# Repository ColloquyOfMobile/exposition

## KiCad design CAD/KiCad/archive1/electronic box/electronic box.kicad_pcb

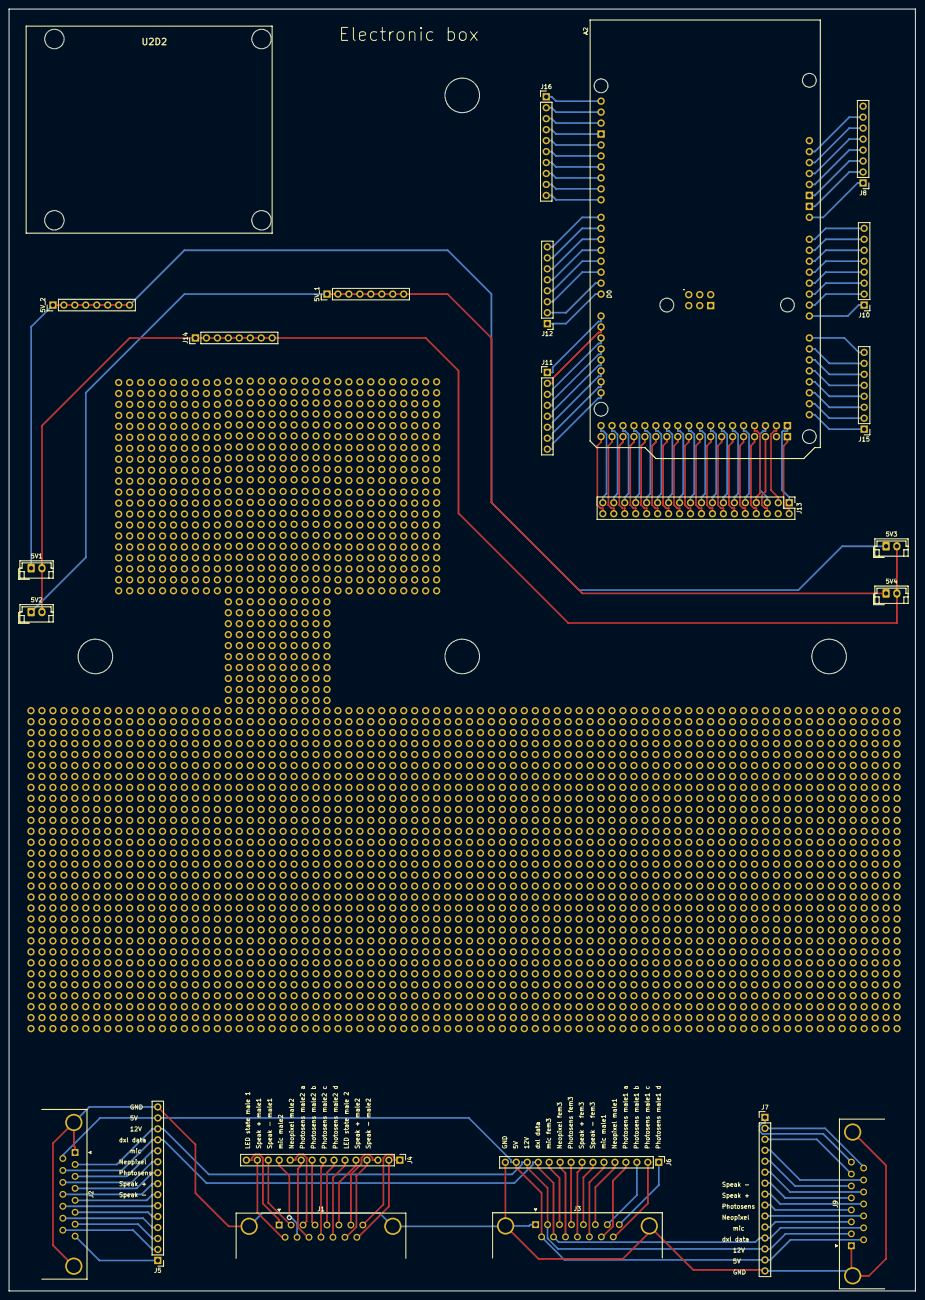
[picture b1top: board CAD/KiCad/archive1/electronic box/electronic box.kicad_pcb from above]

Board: 2 copper layers, 210.0 x 297.0 mm, 54 parts (1 on the bottom side), 139 nets.

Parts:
5V1, 5V3: 5V1; JST_EH_B2B-EH-A_1x02_P2.50mm_Vertical
5V2, 5V4: 5V2; JST_EH_B2B-EH-A_1x02_P2.50mm_Vertical
5V_1, 5V_2: Conn_01x08; PinHeader_1x08_P2.54mm_Vertical
A2: Arduino_Mega2560_R3_Shield
J1: to center B; DSUB-15_Male_Horizontal_P2.77x2.84mm_EdgePinOffset4.94mm_Ho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
J2: to female static 1; DSUB-15_Male_Horizontal_P2.77x2.84mm_EdgePinOffset4.94mm_Ho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
J3: to center A; DSUB-15_Male_Horizontal_P2.77x2.84mm_EdgePinOffset4.94mm_Ho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
J4, J5, J6, J7: Conn_01x15; PinHeader_1x15_P2.54mm_Vertical
J8, J10, J11, J12, J14, J15: Conn_01x08; PinHeader_1x08_P2.54mm_Vertical
J9: to female static 2; DSUB-15_Male_Horizontal_P2.77x2.84mm_EdgePinOffset4.94mm_Ho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
J13: Conn_02x18_Odd_Even; PinHeader_2x18_P2.54mm_Vertical
J16: Conn_01x10; PinHeader_1x10_P2.54mm_Vertical
U1, U2, U3, U4, U5, U6, U7, U8, U9, U10, U11, U12, U13, U14, U15, U16, U17, U18, U19, U20, U21, U22, U23, U24, U25, U26, U27, U28, U29, U30, U31: test_pad_10x10

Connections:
/Arduino Mega/5V3: A2.5V3 (5V), J13.35
/Arduino Mega/5V4: A2.5V4 (5V), J13.36
/Arduino Mega/D0: A2.D0 (D0/RX0), J12.1
/Arduino Mega/D1: A2.D1 (D1/TX0), J12.2
/Arduino Mega/D08: A2.D8, J16.10
/Arduino Mega/D09: A2.D9, J16.9
/Arduino Mega/D10: A2.D10, J16.8
/Arduino Mega/D11: A2.D11, J16.7
/Arduino Mega/D12: A2.D12, J16.6
/Arduino Mega/D13: A2.D13, J16.5
/Arduino Mega/D20: A2.D20 (D20/SDA), J11.7
/Arduino Mega/D21: A2.D21 (D21/SCL), J11.8
/Arduino Mega/D22: A2.D22, J13.33
/Arduino Mega/D23: A2.D23, J13.34
/Arduino Mega/D24: A2.D24, J13.31
/Arduino Mega/D25: A2.D25, J13.32
/Arduino Mega/D26: A2.D26, J13.29
/Arduino Mega/D27: A2.D27, J13.30
/Arduino Mega/D28: A2.D28, J13.27
/Arduino Mega/D29: A2.D29, J13.28
/Arduino Mega/D30: A2.D30, J13.25
/Arduino Mega/D31: A2.D31, J13.26
/Arduino Mega/D32: A2.D32, J13.23
/Arduino Mega/D33: A2.D33, J13.24
/Arduino Mega/D34: A2.D34, J13.21
/Arduino Mega/D35: A2.D35, J13.22
/Arduino Mega/D36: A2.D36, J13.19
/Arduino Mega/D37: A2.D37, J13.20
/Arduino Mega/D38: A2.D38, J13.17
/Arduino Mega/D39: A2.D39, J13.18
/Arduino Mega/D40: A2.D40, J13.15
/Arduino Mega/D41: A2.D41, J13.16
/Arduino Mega/D42: A2.D42, J13.13
/Arduino Mega/D43: A2.D43, J13.14
/Arduino Mega/D44: A2.D44, J13.11
/Arduino Mega/D45: A2.D45, J13.12
/Arduino Mega/D46: A2.D46, J13.9
/Arduino Mega/D47: A2.D47, J13.10
/Arduino Mega/D48: A2.D48, J13.7
/Arduino Mega/D49: A2.D49, J13.8
/Arduino Mega/D50: A2.D50 (D50_MISO), J13.5
/Arduino Mega/D51: A2.D51 (D51_MOSI), J13.6
/Arduino Mega/D52: A2.D52 (D52_SCK), J13.3
/Arduino Mega/GND5: A2.GND5 (GND), J13.1
/Arduino Mega/GND6: A2.GND6 (GND), J13.2
/D-sub connectors/5V: J2.9, J3.9, J5.14, J6.14, J7.14, J9.9
/D-sub connectors/12V: J2.2, J3.2, J5.13, J6.13, J7.13, J9.2
/D-sub connectors/dynamixel data: J2.10, J3.10, J5.12, J6.12, J7.12, J9.10
/D-sub connectors/microphone female output: J3.3, J6.11
/D-sub connectors/microphone female output 1: J2.3, J5.11
/D-sub connectors/microphone female output 2: J7.11, J9.3
/D-sub connectors/microphone male output 1: J3.13, J6.6
/D-sub connectors/microphone male output 2: J1.10, J4.12
/D-sub connectors/neopixel female input: J3.11 (P111), J6.10
/D-sub connectors/neopixel female input 1: J2.11 (P111), J5.10
/D-sub connectors/neopixel female input 2: J7.10, J9.11 (P111)
/D-sub connectors/neopixel male input 1: J3.6, J6.5
/D-sub connectors/neopixel male input 2: J1.3, J4.11
/D-sub connectors/photo sensor female output: J3.4, J6.9
/D-sub connectors/photo sensor female output 1: J2.4, J5.9
/D-sub connectors/photo sensor female output 2: J7.9, J9.4
/D-sub connectors/photo sensor male output 1a: J3.14, J6.4
/D-sub connectors/photo sensor male output 1b: J3.7, J6.3
/D-sub connectors/photo sensor male output 1c: J3.15, J6.2
/D-sub connectors/photo sensor male output 1d: J3.8, J6.1
/D-sub connectors/photo sensor male output 2a: J1.11 (P111), J4.10
/D-sub connectors/photo sensor male output 2b: J1.4, J4.9
/D-sub connectors/photo sensor male output 2c: J1.12, J4.8
/D-sub connectors/photo sensor male output 2d: J1.5, J4.7
/D-sub connectors/speaker female 1 +: J2.12, J5.8
/D-sub connectors/speaker female 1 -: J2.5, J5.7
/D-sub connectors/speaker female 2 +: J7.8, J9.12
/D-sub connectors/speaker female 2 -: J7.7, J9.5
/D-sub connectors/speaker female +: J3.12, J6.8
/D-sub connectors/speaker female -: J3.5, J6.7
/D-sub connectors/speaker male 1 +: J1.9, J4.14
/D-sub connectors/speaker male 1 -: J1.2, J4.13
/D-sub connectors/speaker male 2 +: J1.6, J4.5
/D-sub connectors/speaker male 2 -: J1.14, J4.4
/D-sub connectors/state LED male output 1: J1.1, J4.15
/D-sub connectors/state LED male output 2: J1.13, J4.6
/Pad/5V1: 5V2.1, 5V4.1, 5V_1.1, 5V_1.2, 5V_1.3, 5V_1.4, 5V_1.5, 5V_1.6, 5V_1.7, 5V_1.8
/Pad/5V2: 5V1.1, 5V3.1, 5V_2.1, 5V_2.2, 5V_2.3, 5V_2.4, 5V_2.5, 5V_2.6, 5V_2.7, 5V_2.8
GND: J1.0 (PAD), J2.0 (PAD), J2.1, J3.0 (PAD), J3.1, J5.15, J6.15, J7.15, J9.0 (PAD), J9.1
GND1: 5V1.2, 5V2.2, 5V3.2, 5V4.2, J14.1, J14.2, J14.3, J14.4, J14.5, J14.6, J14.7, J14.8
unnamed: A2.3V3 (3.3V), J8.5
unnamed: A2.D2 (D2_INT0), J12.3
unnamed: A2.D3 (D3_INT1), J12.4
unnamed: A2.D14 (D14/TX3), J11.1
unnamed: A2.D15 (D15/RX3), J11.2
unnamed: A2.D16 (D16/TX2), J11.3
unnamed: A2.D17 (D17/RX2), J11.4
unnamed: A2.D18 (D18/TX1), J11.5
unnamed: A2.D19 (D19/RX1), J11.6
unnamed: A2.IORF (IOREF), J8.7
unnamed: A2.RST1 (RESET), J8.6
unnamed: J1.15, J4.2
unnamed: J2.13, J5.6
unnamed: J2.14, J5.4
unnamed: J2.15, J5.2
unnamed: J1.8, J4.1
unnamed: J1.7, J4.3
unnamed: J2.8, J5.1
unnamed: J2.7, J5.3
unnamed: J2.6, J5.5
unnamed: J7.1, J9.8
unnamed: J7.2, J9.15
unnamed: J7.3, J9.7
unnamed: J7.4, J9.14
unnamed: J7.5, J9.6
unnamed: J7.6, J9.13
unnamed: A2.VIN, J8.1
unnamed: A2.GND3 (GND), J8.2
unnamed: A2.GND2 (GND), J8.3
unnamed: A2.5V1 (5V), J8.4
unnamed: A2.A7, J10.1
unnamed: A2.A6, J10.2
unnamed: A2.A5, J10.3
unnamed: A2.A4, J10.4
unnamed: A2.A3, J10.5
unnamed: A2.A2, J10.6
unnamed: A2.A1, J10.7
unnamed: A2.A0, J10.8
unnamed: A2.D4, J12.5
unnamed: A2.D5, J12.6
unnamed: A2.D6, J12.7
unnamed: A2.D7, J12.8
unnamed: A2.A15, J15.1
unnamed: A2.A14, J15.2
unnamed: A2.A13, J15.3
unnamed: A2.A12, J15.4
unnamed: A2.A11, J15.5
unnamed: A2.A10, J15.6
unnamed: A2.A9, J15.7
unnamed: A2.A8, J15.8
unnamed: A2.SCL, J16.1
unnamed: A2.SDA, J16.2
unnamed: A2.AREF, J16.3
unnamed: A2.GND1 (GND), J16.4

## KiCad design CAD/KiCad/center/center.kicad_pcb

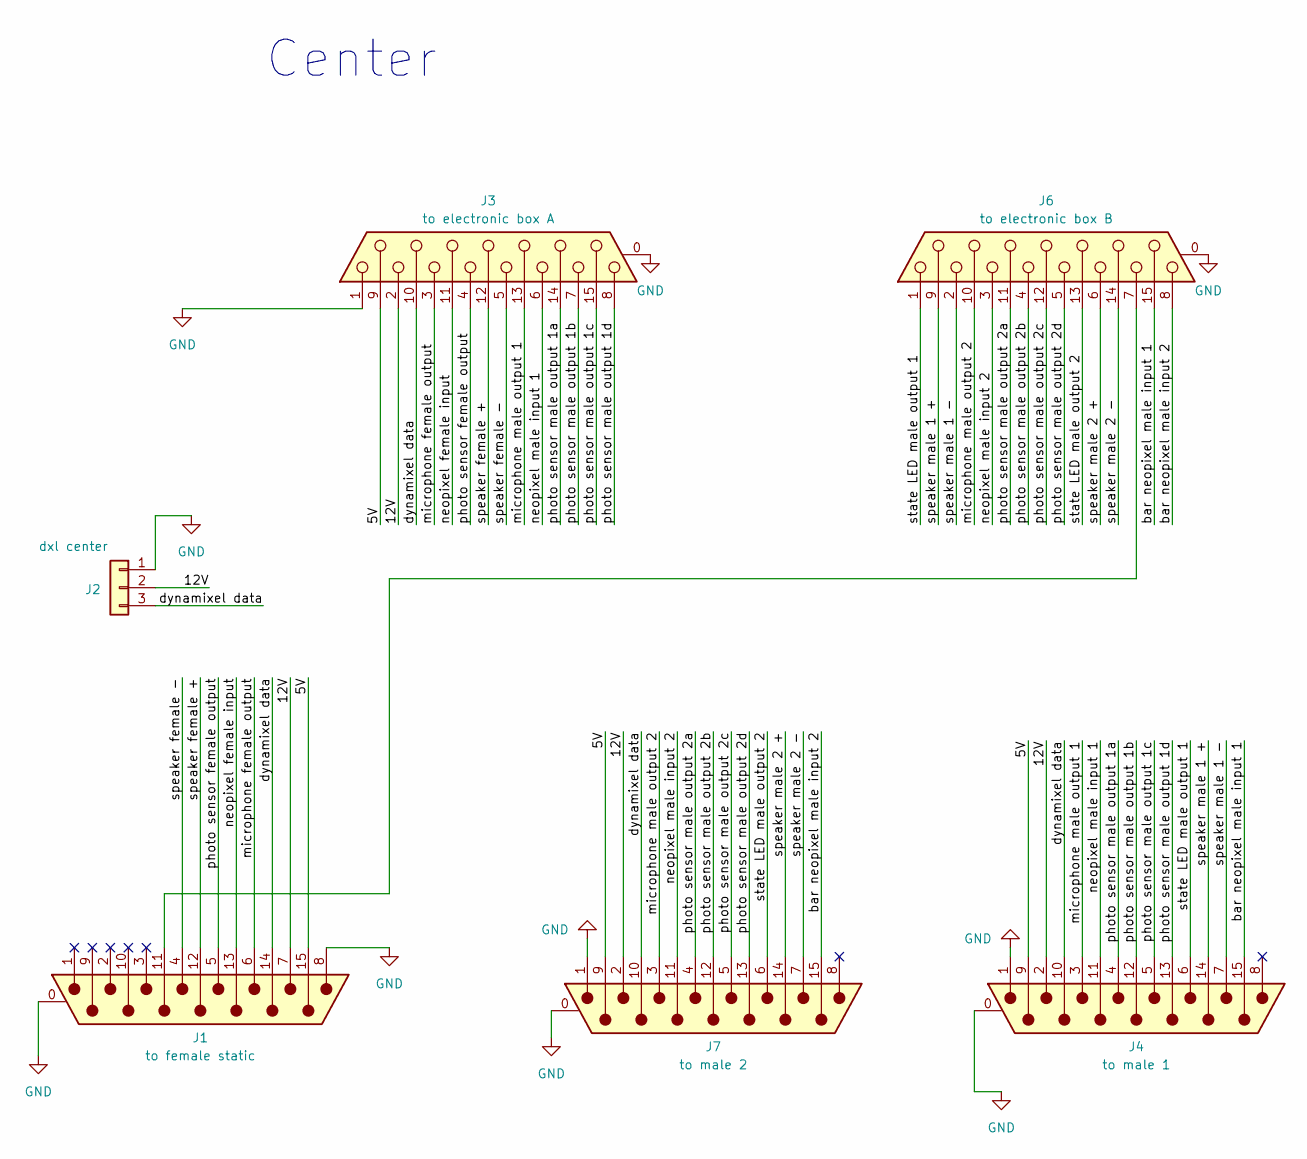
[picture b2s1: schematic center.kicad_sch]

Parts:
J1: to female static; DSUB-15_Male_Horizontal_P2.77x2.84mm_EdgePinOffset4.94mm_Ho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
J2: dxl center; JST_EH_B3B-EH-A_1x03_P2.50mm_Vertical
J3: to electronic box A; DSUB-15_Female_Horizontal_P2.77x2.84mm_EdgePinOffset4.94mm_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
J4: to male 1; DSUB-15_Male_Horizontal_P2.77x2.84mm_EdgePinOffset4.94mm_Ho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
J6: to electronic box B; DSUB-15_Female_Horizontal_P2.77x2.84mm_EdgePinOffset4.94mm_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
J7: to male 2; DSUB-15_Male_Horizontal_P2.77x2.84mm_EdgePinOffset4.94mm_Ho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

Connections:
/5V: J1.15, J3.9, J4.9, J7.9
/12V: J1.7, J2.2, J3.2, J4.2, J7.2
/bar neopixel male input 1: J4.15, J6.15
/bar neopixel male input 2: J6.8, J7.15
/dynamixel data: J1.14, J2.3, J3.10, J4.10, J7.10
/microphone female output: J1.6, J3.3
/microphone male output 1: J3.13, J4.3
/microphone male output 2: J6.10, J7.3
/neopixel female input: J1.13, J3.11 (P111)
/neopixel male input 1: J3.6, J4.11 (P111)
/neopixel male input 2: J6.3, J7.11 (P111)
/photo sensor female output: J1.5, J3.4
/photo sensor male output 1a: J3.14, J4.4
/photo sensor male output 1b: J3.7, J4.12
/photo sensor male output 1c: J3.15, J4.5
/photo sensor male output 1d: J3.8, J4.13
/photo sensor male output 2a: J6.11 (P111), J7.4
/photo sensor male output 2b: J6.4, J7.12
/photo sensor male output 2c: J6.12, J7.5
/photo sensor male output 2d: J6.5, J7.13
/speaker female +: J1.12, J3.12
/speaker female -: J1.4, J3.5
/speaker male 1 +: J4.14, J6.9
/speaker male 1 -: J4.7, J6.2
/speaker male 2 +: J6.6, J7.14
/speaker male 2 -: J6.14, J7.7
/state LED male output 1: J4.6, J6.1
/state LED male output 2: J6.13, J7.6
GND: J1.0 (PAD), J1.8, J2.1, J3.0 (PAD), J3.1, J4.0 (PAD), J4.1, J6.0 (PAD), J7.0 (PAD), J7.1
unnamed: J1.11 (P111), J6.7

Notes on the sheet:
Center

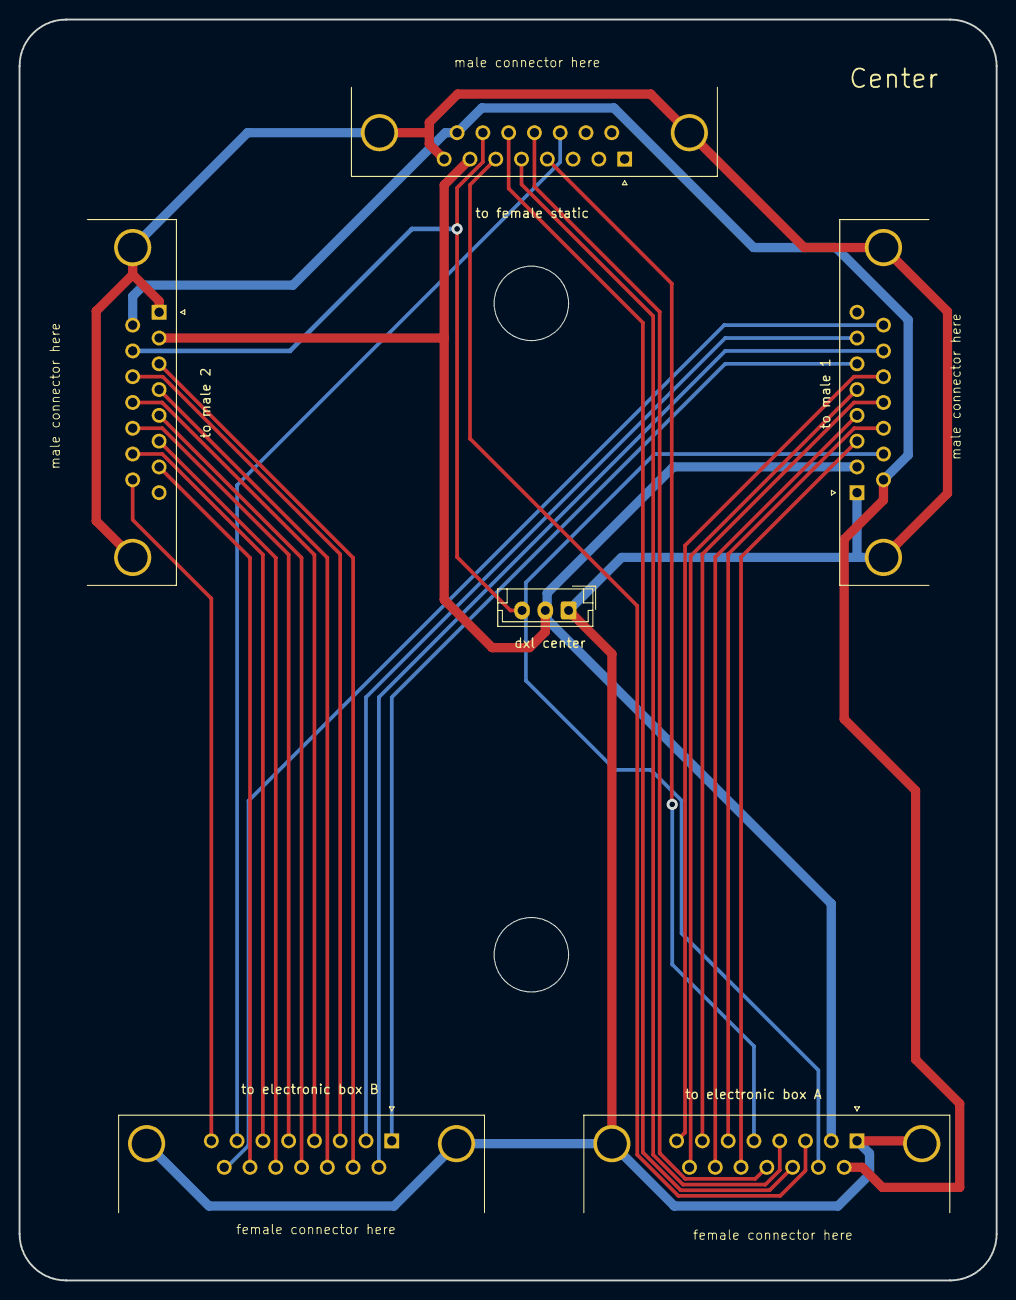
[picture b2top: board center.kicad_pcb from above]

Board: 2 copper layers, 105.0 x 135.5 mm, 6 parts (0 on the bottom side), 30 nets.

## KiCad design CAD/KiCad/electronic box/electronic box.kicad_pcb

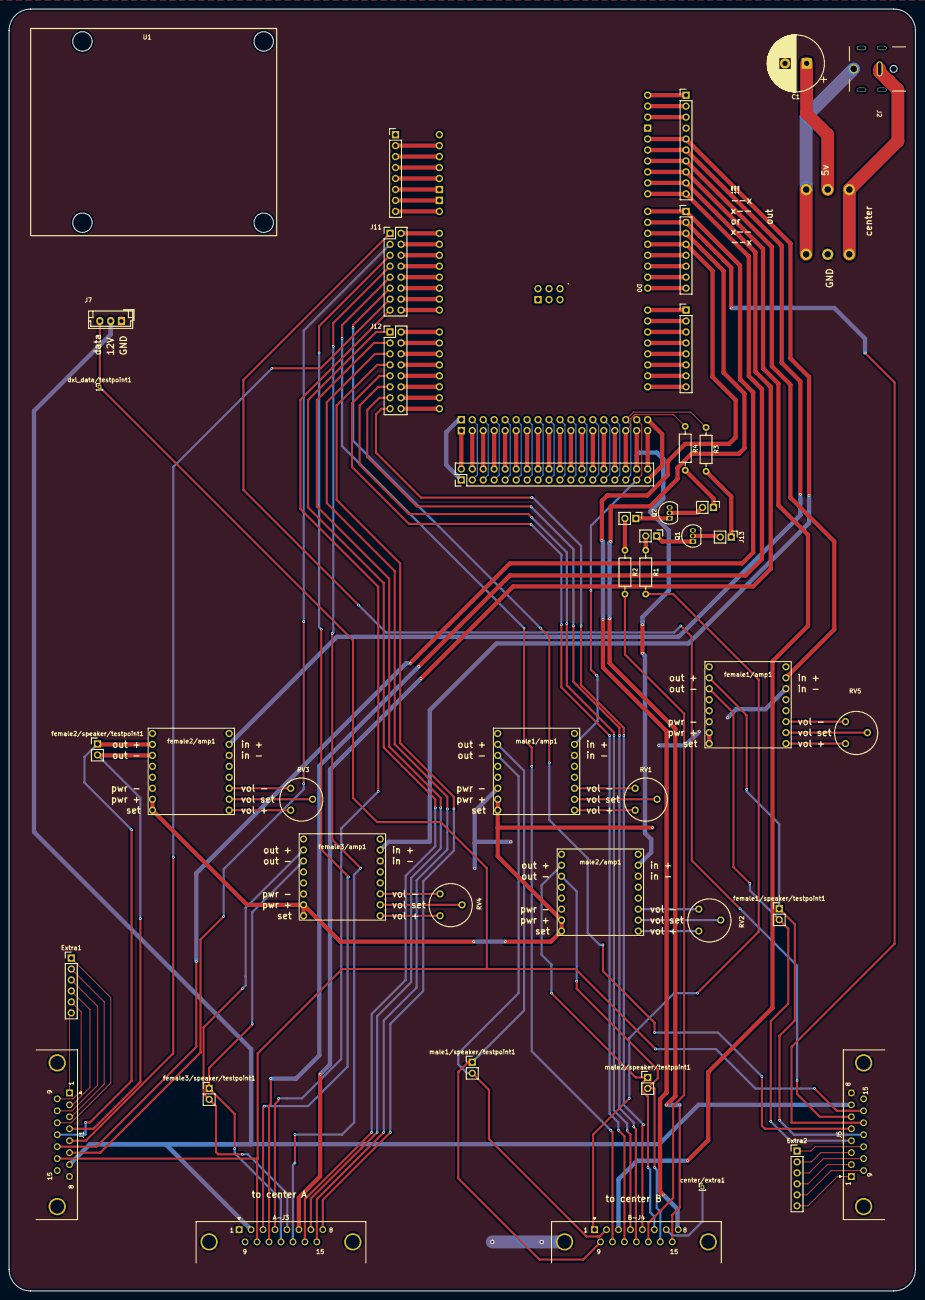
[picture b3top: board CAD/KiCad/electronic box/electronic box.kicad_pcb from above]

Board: 2 copper layers, 210.0 x 297.0 mm, 46 parts (0 on the bottom side), 154 nets.

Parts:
A1: Arduino_Mega2560_R3_Shield
A-J3: DA15_Socket_MountingHoles; DSUB-15_Pins_Horizontal_P2.77x2.84mm_EdgePinOffset4.94mm_Ho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
B-J4: DA15_Socket_MountingHoles; DSUB-15_Pins_Horizontal_P2.77x2.84mm_EdgePinOffset4.94mm_Ho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
C1: C_Polarized; CP_Radial_D13.0mm_P5.00mm
Extra1, Extra2: Conn_01x06; PinHeader_1x06_P2.54mm_Vertical
J1, J5: DA15_Socket_MountingHoles; DSUB-15_Pins_Horizontal_P2.77x2.84mm_EdgePinOffset4.94mm_Ho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
J2: Jack-DC; PJ-082BH jack 10A
J3: Conn_01x06; PinHeader_1x08_P2.54mm_Vertical
J4: Conn_01x10; PinHeader_1x10_P2.54mm_Vertical
J6: Conn_02x03_Counter_Clockwise; screw brigde
J7: Conn_01x03; JST_EH_B3B-EH-A_1x03_P2.50mm_Vertical
J8, J10: Conn_01x08; PinHeader_1x08_P2.54mm_Vertical
J9: Conn_02x18_Odd_Even; PinHeader_2x18_P2.54mm_Vertical
J11, J12: Conn_02x08_Odd_Even; PinHeader_2x08_P2.54mm_Vertical
J13, J14, J15, J16: Conn_01x02; PinHeader_1x02_P2.54mm_Vertical
Q1, Q2: BC557; TO-92_Inline
R1, R2: 150; R_Axial_DIN0207_L6.3mm_D2.5mm_P10.16mm_Horizontal
R3, R4: 10k; R_Axial_DIN0207_L6.3mm_D2.5mm_P10.16mm_Horizontal
RV1, RV2, RV3, RV4, RV5: R_Potentiometer; custom potentiometer 1
U1: u2d2_mounting
center/extra1: Conn_01x01; PinHeader_1x01_P1.00mm_Vertical
dxl_data/testpoint1: Conn_01x01; PinHeader_1x01_P1.00mm_Vertical
female1/amp1, female2/amp1, female3/amp1: SparkFun Mono Audio Amp Breakout TPA2005D1
female1/speaker/testpoint1, female2/speaker/testpoint1, female3/speaker/testpoint1: Conn_01x01; PinHeader_1x02_P2.54mm_Vertical
male1/amp1, male2/amp1: SparkFun Mono Audio Amp Breakout TPA2005D1
male1/speaker/testpoint1, male2/speaker/testpoint1: Conn_01x01; PinHeader_1x02_P2.54mm_Vertical

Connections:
+3.3V: A1.3V3 (3.3V), J3.4
+5V: A-J3.9, C1.1, J1.15, J5.15, J6.3, Q1.3 (E), Q2.3 (E), female1/amp1.4 (pwr_+), female1/amp1.5 (set), female2/amp1.4 (pwr_+), female2/amp1.5 (set), female3/amp1.4 (pwr_+), female3/amp1.5 (set), male1/amp1.4 (pwr_+), male1/amp1.5 (set), male2/amp1.4 (pwr_+), male2/amp1.5 (set)
+12V: A-J3.2, J1.7, J5.7, J7.2
/5V1: A1.5V1 (5V), J3.5
/5V3: A1.5V3 (5V), J9.35
/5V4: A1.5V4 (5V), J9.36
/AREF: A1.AREF, J4.3
/D0: A1.D0 (D0/RX0), J8.8
/D1: A1.D1 (D1/TX0), J8.7
/D2: A1.D2 (D2_INT0), J8.6
/D3: A1.D3 (D3_INT1), J8.5
/D14: A1.D14 (D14/TX3), J10.1
/D15: A1.D15 (D15/RX3), J10.2
/D16: A1.D16 (D16/TX2), J10.3
/D17: A1.D17 (D17/RX2), J10.4
/D18: A1.D18 (D18/TX1), J10.5
/D19: A1.D19 (D19/RX1), J10.6
/D20: A1.D20 (D20/SDA), J10.7
/D21: A1.D21 (D21/SCL), J10.8
/D24: A1.D24, J9.31, R3.1
/D25: A1.D25, J9.32, R4.1
/D26: A1.D26, J9.29
/D27: A1.D27, J9.30
/D28: A1.D28, J9.27
/D29: A1.D29, J9.28
/D30: A1.D30, J9.25
/D31: A1.D31, J9.26
/D32: A1.D32, J9.23
/D33: A1.D33, J9.24
/D34: A1.D34, J9.21
/D35: A1.D35, J9.22
/D36: A1.D36, J9.19
/D37: A1.D37, J9.20
/D38: A1.D38, J9.17
/D39: A1.D39, J9.18
/D40: A1.D40, J9.15
/D41: A1.D41, J9.16
/D42: A1.D42, J9.13
/D43: A1.D43, J9.14
/D44: A1.D44, J9.11
/D45: A1.D45, J9.12
/D46: A1.D46, J9.9
/D47: A1.D47, J9.10
/D48: A1.D48, J9.7
/D49: A1.D49, J9.8
/D50_MISO: A1.D50 (D50_MISO), J9.5
/D51_MOSI: A1.D51 (D51_MOSI), J9.6
/D52_SCK: A1.D52 (D52_SCK), J9.3
/D53_CS: A1.D53 (D53_CS), J9.4
/GND5: A1.GND5 (GND), J9.1
/GND6: A1.GND6 (GND), J9.2
/IOREF: A1.IORF (IOREF), J3.2
/RST1: A1.RST1 (RESET), J3.3
/SCL: A1.SCL, J4.1
/SDA: A1.SDA, J4.2
/dxl_data: A-J3.10, J1.14, J5.14, J7.3, dxl_data/testpoint1.1
/female1/audio: A1.D11, J4.7, female1/amp1.6 (in_+)
/female1/microphone/1: J5.6, J11.1
/female1/microphone/2: A1.A0, J11.2
/female1/neopixel: A1.D6, J5.13, J8.2
/female1/photosensor/1: J5.5, J11.11
/female1/photosensor/2: A1.A5, J11.12
/female1/speaker +/out: J5.12, female1/amp1.1 (out_+), female1/speaker/testpoint1.1
/female1/speaker -/out: J5.4, female1/amp1.2 (out_-), female1/speaker/testpoint1.2
/female2/audio: A1.D12, J4.6, female2/amp1.6 (in_+)
/female2/microphone/1: J1.6, J11.3
/female2/microphone/2: A1.A1, J11.4
/female2/neopixel: A1.D7, J1.13, J8.1
/female2/photosensor/1: J1.5, J11.13
/female2/photosensor/2: A1.A6, J11.14
/female2/speaker +/out: J1.12, female2/amp1.1 (out_+), female2/speaker/testpoint1.1
/female2/speaker -/out: J1.4, female2/amp1.2 (out_-), female2/speaker/testpoint1.2
/female3/audio: A1.D13, J4.5, female3/amp1.6 (in_+)
/female3/microphone/1: A-J3.3, J11.5
/female3/microphone/2: A1.A2, J11.6
/female3/neopixel: A1.D8, A-J3.11 (P111), J4.10
/female3/photosensor/1: A-J3.4, J11.15
/female3/photosensor/2: A1.A7, J11.16
/female3/speaker +/out: A-J3.12, female3/amp1.2 (out_-), female3/speaker/testpoint1.1
/female3/speaker -/out: A-J3.5, female3/amp1.1 (out_+), female3/speaker/testpoint1.2
/male1/audio: A1.D22, J9.33, male1/amp1.6 (in_+)
/male1/bar neopixel: A1.D5, B-J4.15, J8.3
/male1/microphone/1: A-J3.13, J11.7
/male1/microphone/2: A1.A3, J11.8
/male1/neopixel: A1.D9, A-J3.6, J4.9
/male1/photosensor/A/1: A-J3.14, J12.1
/male1/photosensor/A/2: A1.A8, J12.2
/male1/photosensor/B/1: A-J3.7, J12.3
/male1/photosensor/B/2: A1.A9, J12.4
/male1/photosensor/C/1: A-J3.15, J12.5
/male1/photosensor/C/2: A1.A10, J12.6
/male1/photosensor/D/1: A-J3.8, J12.7
/male1/photosensor/D/2: A1.A11, J12.8
/male1/speaker +/out: B-J4.9, male1/amp1.1 (out_+), male1/speaker/testpoint1.1
/male1/speaker -/out: B-J4.2, male1/amp1.2 (out_-), male1/speaker/testpoint1.2
/male1/state LED: B-J4.1, R1.2
/male2/audio: A1.D23, J9.34, male2/amp1.6 (in_+)
/male2/bar neopixel: A1.D4, B-J4.8, J8.4
/male2/microphone/1: B-J4.10, J11.9
/male2/microphone/2: A1.A4, J11.10
/male2/neopixel: A1.D10, B-J4.3, J4.8
/male2/photosensor/A/1: B-J4.11 (P111), J12.9
/male2/photosensor/A/2: A1.A12, J12.10
/male2/photosensor/B/1: B-J4.4, J12.11
/male2/photosensor/B/2: A1.A13, J12.12
/male2/photosensor/C/1: B-J4.12, J12.13
/male2/photosensor/C/2: A1.A14, J12.14
/male2/photosensor/D/1: B-J4.5, J12.15
/male2/photosensor/D/2: A1.A15, J12.16
/male2/speaker +/out: B-J4.6, male2/amp1.1 (out_+), male2/speaker/testpoint1.1
/male2/speaker -/out: B-J4.14, male2/amp1.2 (out_-), male2/speaker/testpoint1.2
/male2/state LED: B-J4.13, R2.2
/volume1: RV3.2, female2/amp1.9 (vol_set)
/volume2: RV1.2, male1/amp1.9 (vol_set)
/volume3: RV5.2, female1/amp1.9 (vol_set)
/volume4: RV4.2, female3/amp1.9 (vol_set)
/volume5: RV2.2, male2/amp1.9 (vol_set)
GND: A1.GND1 (GND), A-J3.0 (PAD), A-J3.1, B-J4.0 (PAD), C1.2, J1.0 (PAD), J1.8, J4.4, J5.0 (PAD), J5.8, J6.4, J7.1, female1/amp1.3 (pwr_-), female1/amp1.7 (in_-), female2/amp1.3 (pwr_-), female2/amp1.7 (in_-), female3/amp1.3 (pwr_-), female3/amp1.7 (in_-), male1/amp1.3 (pwr_-), male1/amp1.7 (in_-), male2/amp1.3 (pwr_-), male2/amp1.7 (in_-)
GND2: A1.GND2 (GND), J3.6
GND3: A1.GND3 (GND), J3.7
unnamed: Extra1.1, J1.11 (P111)
unnamed: Extra1.2, J1.3
unnamed: Extra1.3, J1.10
unnamed: Extra1.4, J1.2
unnamed: Extra1.5, J1.9
unnamed: Extra1.6, J1.1
unnamed: Extra2.1, J5.11 (P111)
unnamed: Extra2.2, J5.3
unnamed: Extra2.3, J5.10
unnamed: Extra2.4, J5.2
unnamed: Extra2.5, J5.9
unnamed: Extra2.6, J5.1
unnamed: A1.VIN, J3.8
unnamed: J2.2, J6.1, J6.2
unnamed: J2.1, J6.5, J6.6
unnamed: J13.1, R3.2
unnamed: J13.2, Q1.2 (B)
unnamed: J14.1, R4.2
unnamed: J14.2, Q2.2 (B)
unnamed: J15.1, Q1.1 (C)
unnamed: J15.2, R1.1
unnamed: J16.1, Q2.1 (C)
unnamed: J16.2, R2.1
unnamed: B-J4.7, center/extra1.1
unnamed: RV5.1, female1/amp1.10 (vol_+)
unnamed: RV5.3, female1/amp1.8 (vol_-)
unnamed: RV3.1, female2/amp1.10 (vol_+)
unnamed: RV3.3, female2/amp1.8 (vol_-)
unnamed: RV4.1, female3/amp1.10 (vol_+)
unnamed: RV4.3, female3/amp1.8 (vol_-)
unnamed: RV1.1, male1/amp1.10 (vol_+)
unnamed: RV1.3, male1/amp1.8 (vol_-)
unnamed: RV2.1, male2/amp1.10 (vol_+)
unnamed: RV2.3, male2/amp1.8 (vol_-)

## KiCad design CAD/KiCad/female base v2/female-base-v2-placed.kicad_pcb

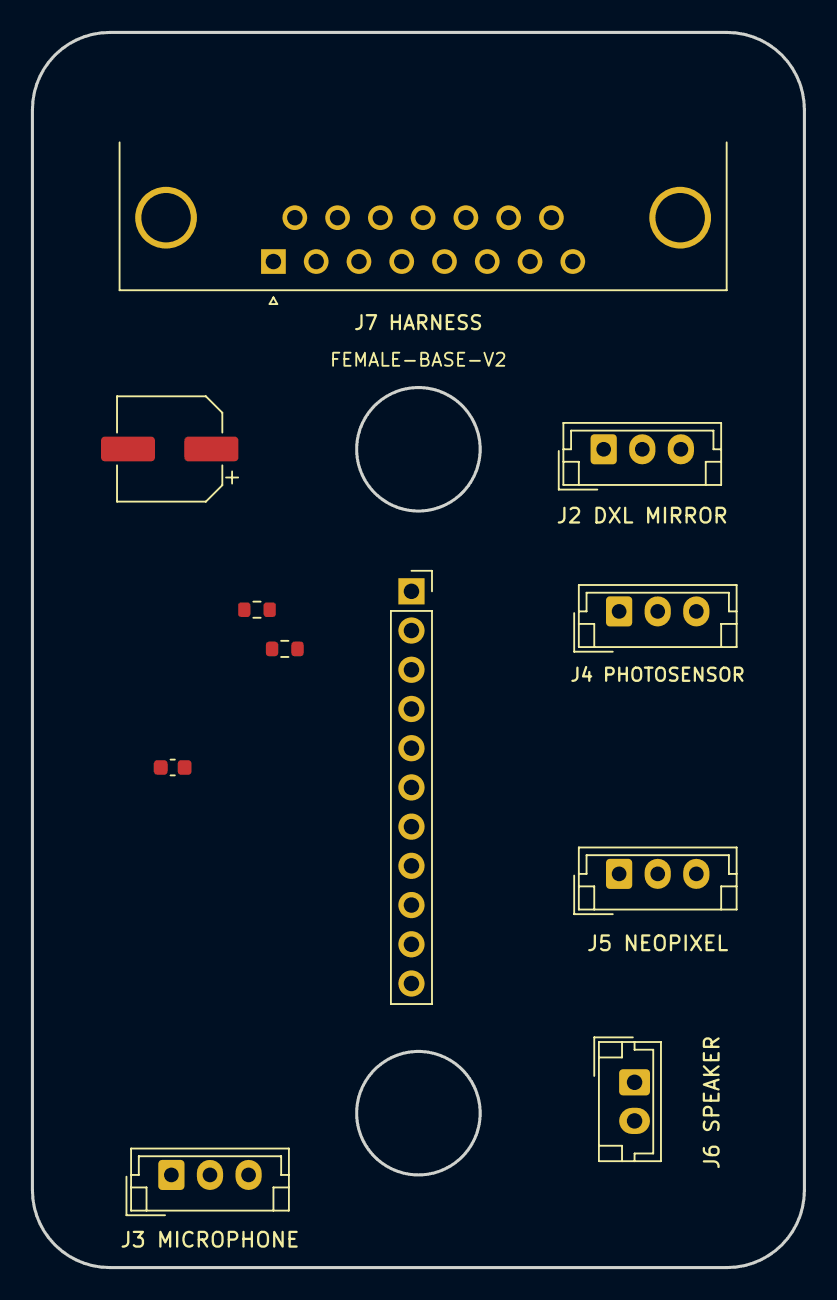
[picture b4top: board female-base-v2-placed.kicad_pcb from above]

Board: 2 copper layers, 50.0 x 80.0 mm, 11 parts (0 on the bottom side), 12 nets, no tracks yet.

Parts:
C1: 220uF 10V / provisional; CP_Elec_6.3x5.8
C2: 100nF; C_0603_1608Metric
J2: dxl mirror; J2_original
J3: microphone; J3_original
J4: photosensor; J4_original
J5: neopixel; J5_original
J6: Speaker; J6_original
J7: DA15_Plug_MountingHoles; J7_original
M1: GF1002 / 1x11 female socket; GF1002_PlugIn_1x11
R1: 22K; R_0603_1608Metric
R2: 3K3; R_0603_1608Metric

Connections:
5V: C1.1, C2.1, J3.2, J4.2, J5.2, J7.15, M1.5
12V: J2.2, J7.7
AMP_INPUT: M1.1, R1.2, R2.1
AMP_OUT_N: J6.2, M1.11
AMP_OUT_P: J6.1, M1.10
AUDIO_RETURN: J7.4, M1.2, R2.2
GND: C1.2, C2.2, J2.1, J3.1, J4.1, J5.1, J7.0, J7.8, M1.6
LINE_IN: J7.12, R1.1
dynamixel data: J2.3, J7.14
microphone output: J3.3, J7.6
neopixel input: J5.3, J7.13
photo sensor output: J4.3, J7.5

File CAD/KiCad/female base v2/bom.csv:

Reference,Value,Footprint,Description
J4,photosensor,Body:J4_original,Original harness pin order retained. J6 now carries the local amplifier output.
J2,dxl mirror,Body:J2_original,Original harness pin order retained. J6 now carries the local amplifier output.
J7,DA15_Plug_MountingHoles,Body:J7_original,Original harness pin order retained. J6 now carries the local amplifier output.
J3,microphone,Body:J3_original,Original harness pin order retained. J6 now carries the local amplifier output.
J5,neopixel,Body:J5_original,Original harness pin order retained. J6 now carries the local amplifier output.
J6,Speaker,Body:J6_original,Original harness pin order retained. J6 now carries the local amplifier output.
R1,22K,Resistor_SMD:R_0603_1608Metric,
R2,3K3,Resistor_SMD:R_0603_1608Metric,
C1,220uF 10V / provisional,Capacitor_THT:CP_Radial_D6.3mm_P2.50mm,Provisional local reservoir; verify actual amplifier transients and rail sag before release.
C2,100nF,Capacitor_SMD:C_0603_1608Metric,
M1,GF1002 / 1x11 female socket,Body:GF1002_PlugIn_1x11,"Plug-in module: 1x3, 1x2 and 1x4 downward male headers in an 11-pin female socket. Nominal underside gap 11mm. Pin 10=ROUT+, 11=ROUT- is provisional: verify module polarity before ordering."

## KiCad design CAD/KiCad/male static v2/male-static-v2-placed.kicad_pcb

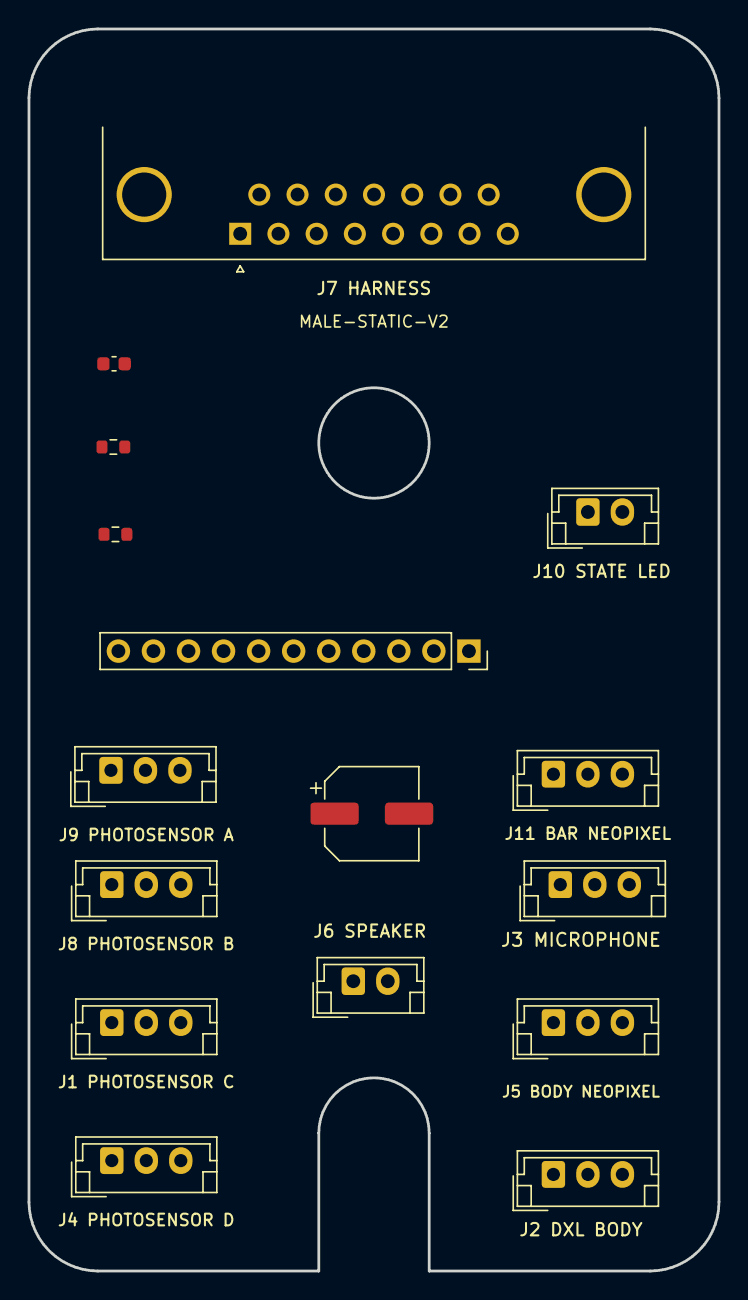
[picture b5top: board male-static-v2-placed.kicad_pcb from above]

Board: 2 copper layers, 50.0 x 90.0 mm, 16 parts (0 on the bottom side), 17 nets, no tracks yet.

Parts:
C1: 220uF 10V / provisional; CP_Elec_6.3x5.8
C2: 100nF; C_0603_1608Metric
J1: photosensor; J1_original
J2: dxl male; J2_original
J3: microphone; J3_original
J4: photosensor; J4_original
J5: body neopixel; J5_original
J6: Speaker; J6_original
J7: DA15_Plug_MountingHoles; J7_original
J8: photosensor; J8_original
J9: photosensor; J9_original
J10: State LED; J10_original
J11: bar neopixel; J11_original
M1: GF1002 / 1x11 female socket; GF1002_PlugIn_1x11
R1: 22K; R_0603_1608Metric
R2: 3K3; R_0603_1608Metric

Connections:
5V: C1.1, C2.1, J1.2, J3.2, J4.2, J5.2, J7.9, J8.2, J9.2, J11.2, M1.5
12V: J2.2, J7.2
AMP_INPUT: M1.1, R1.2, R2.1
AMP_OUT_N: J6.2, M1.11
AMP_OUT_P: J6.1, M1.10
AUDIO_RETURN: J7.7, M1.2, R2.2
GND: C1.2, C2.2, J1.1, J2.1, J3.1, J4.1, J5.1, J7.0, J7.1, J8.1, J9.1, J10.1, J11.1, M1.6
LINE_IN: J7.14, R1.1
bar neopixel male input: J7.15, J11.3
body neopixel male input: J5.3, J7.11
dynamixel data: J2.3, J7.10
microphone male output: J3.3, J7.3
photo sensor male output a: J7.4, J9.3
photo sensor male output b: J7.12, J8.3
photo sensor male output c: J1.3, J7.5
photo sensor male output d: J4.3, J7.13
state LED male output: J7.6, J10.2

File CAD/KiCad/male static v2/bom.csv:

Reference,Value,Footprint,Description
J5,body neopixel,Body:J5_original,Original harness pin order retained. J6 now carries the local amplifier output.
J3,microphone,Body:J3_original,Original harness pin order retained. J6 now carries the local amplifier output.
J11,bar neopixel,Body:J11_original,Original harness pin order retained. J6 now carries the local amplifier output.
J1,photosensor,Body:J1_original,Original harness pin order retained. J6 now carries the local amplifier output.
J7,DA15_Plug_MountingHoles,Body:J7_original,Original harness pin order retained. J6 now carries the local amplifier output.
J4,photosensor,Body:J4_original,Original harness pin order retained. J6 now carries the local amplifier output.
J2,dxl male,Body:J2_original,Original harness pin order retained. J6 now carries the local amplifier output.
J6,Speaker,Body:J6_original,Original harness pin order retained. J6 now carries the local amplifier output.
J10,State LED,Body:J10_original,Original harness pin order retained. J6 now carries the local amplifier output.
J8,photosensor,Body:J8_original,Original harness pin order retained. J6 now carries the local amplifier output.
J9,photosensor,Body:J9_original,Original harness pin order retained. J6 now carries the local amplifier output.
R1,22K,Resistor_SMD:R_0603_1608Metric,
R2,3K3,Resistor_SMD:R_0603_1608Metric,
C1,220uF 10V / provisional,Capacitor_SMD:CP_Elec_6.3x5.8,"SMD polarized aluminium electrolytic, 6.3x5.8mm; pin 1 positive. Provisional local reservoir; verify actual amplifier transients and rail sag before release."
C2,100nF,Capacitor_SMD:C_0603_1608Metric,
M1,GF1002 / 1x11 female socket,Body:GF1002_PlugIn_1x11,"Plug-in module: 1x3, 1x2 and 1x4 downward male headers in an 11-pin female socket. Nominal underside gap 11mm. Pin 10=ROUT+, 11=ROUT- is provisional: verify module polarity before ordering."
